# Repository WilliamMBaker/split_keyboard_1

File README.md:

# split_keyboard_1

Split keyboard project akin to [this](https://www.graz.io/articles/bayleaf-wireless-keyboard) one, and [this](https://github.com/merrittlj/aurora40) one.

## Requirements

- Split, preferably reversible PCBs or at least both sides be manufactured together and snapped/cut appart.
- Large battery, months long battery life.
- Wireless, bluetooth connection to target device.
- Plug and play, HID complient(?).
- Low profile, switches and keycaps.
- Ortholinear and no saggering.

## ErgoGen

[Link](https://ergogen.cache.works/).

## ZMK

[Link](https://zmk.dev/)

## Layout
[Link](https://www.keyboard-layout-editor.com/)

## Resources

- [Nice!Nano v2](https://mechboards.co.uk/products/nice-nano-v2)
- [Choc switches](https://typeractive.xyz/products/choc-switches)
- [Hot swap sockets](https://typeractive.xyz/products/hotswap-sockets?variant=45742200324327)
- [Switches](https://typeractive.xyz/products/mbk-keycaps)
- [Power switches](https://typeractive.xyz/products/power-switch)
- [Diods](https://typeractive.xyz/products/smd-diodes)

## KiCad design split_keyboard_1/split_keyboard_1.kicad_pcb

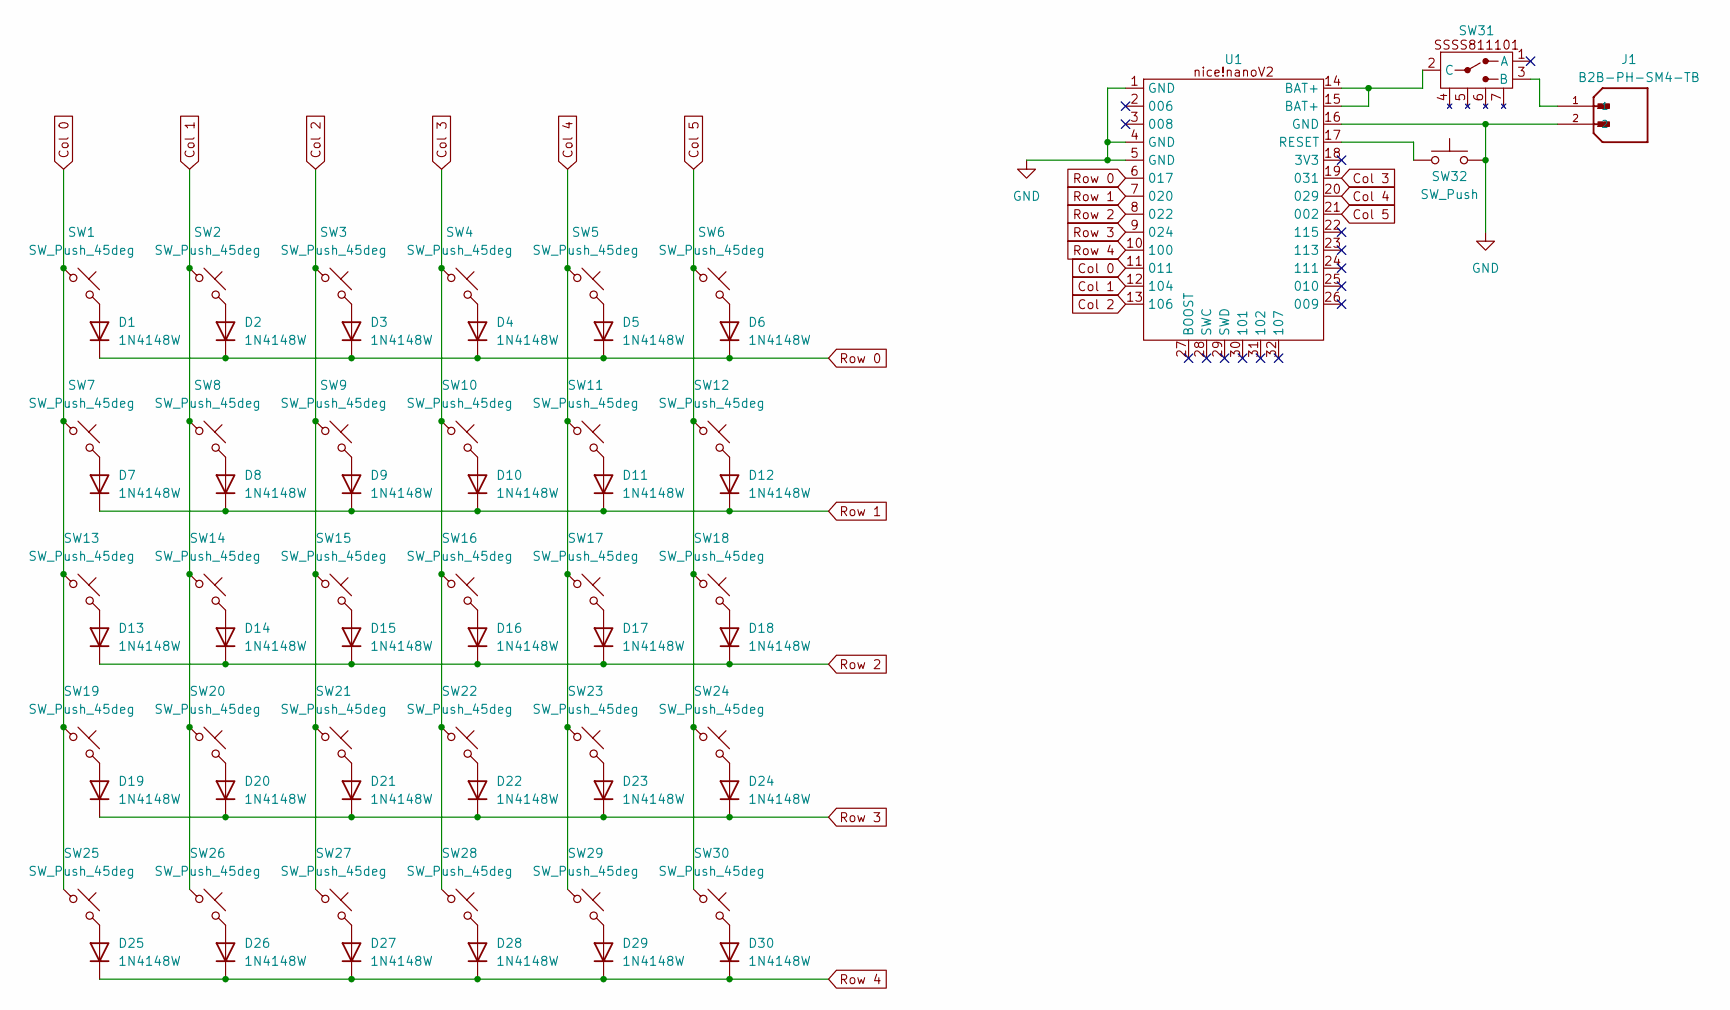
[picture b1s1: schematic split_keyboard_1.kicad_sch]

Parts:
D1, D2, D3, D4, D5, D6, D7, D8, D9, D10, D11, D12, D13, D14, D15, D16, D17, D18, D19, D20, D21, D22, D23, D24, D25, D26, D27, D28, D29, D30: 1N4148W; D_SOD-123
J1: B2B-PH-SM4-TB; JST_GH_SM02B-GHS-TB_1x02-1MP_P1.25mm_Horizontal; PARTREV N/A
SW1, SW2, SW3, SW4, SW5, SW6, SW7, SW8, SW9, SW10, SW11, SW12, SW13, SW14, SW15, SW16, SW17, SW18, SW19, SW20, SW21, SW22, SW23, SW24, SW25, SW26, SW27, SW28, SW29, SW30: SW_Push_45deg; SW_Hotswap_Kailh_Choc_V1_1.00u
SW31: SSSS811101_SW_SPDT
SW32: SW_Push; EVQPU_BTN
U1: nice!nanoV2

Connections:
Col 0: SW1.1, SW7.1, SW13.1, SW19.1, SW25.1, U1.11
Col 1: SW2.1, SW8.1, SW14.1, SW20.1, SW26.1, U1.12 (104)
Col 2: SW3.1, SW9.1, SW15.1, SW21.1, SW27.1, U1.13 (106)
Col 3: SW4.1, SW10.1, SW16.1, SW22.1, SW28.1, U1.19 (031)
Col 4: SW5.1, SW11.1, SW17.1, SW23.1, SW29.1, U1.20 (029)
Col 5: SW6.1, SW12.1, SW18.1, SW24.1, SW30.1, U1.21 (002)
GND: J1.2, SW32.2, U1.1 (GND), U1.4 (GND), U1.5 (GND), U1.16 (GND)
unnamed: D1.2 (A), SW1.2
unnamed: D2.2 (A), SW2.2
unnamed: D3.2 (A), SW3.2
unnamed: D4.2 (A), SW4.2
unnamed: D5.2 (A), SW5.2
unnamed: D6.2 (A), SW6.2
unnamed: D7.2 (A), SW7.2
unnamed: D8.2 (A), SW8.2
unnamed: D9.2 (A), SW9.2
unnamed: D10.2 (A), SW10.2
unnamed: D11.2 (A), SW11.2
unnamed: D12.2 (A), SW12.2
unnamed: D13.2 (A), SW13.2
unnamed: D14.2 (A), SW14.2
unnamed: D15.2 (A), SW15.2
unnamed: D16.2 (A), SW16.2
unnamed: D17.2 (A), SW17.2
unnamed: D18.2 (A), SW18.2
unnamed: D19.2 (A), SW19.2
unnamed: D20.2 (A), SW20.2
unnamed: D21.2 (A), SW21.2
unnamed: D22.2 (A), SW22.2
unnamed: D23.2 (A), SW23.2
unnamed: D24.2 (A), SW24.2
unnamed: D25.2 (A), SW25.2
unnamed: D26.2 (A), SW26.2
unnamed: D27.2 (A), SW27.2
unnamed: D28.2 (A), SW28.2
unnamed: D29.2 (A), SW29.2
unnamed: D30.2 (A), SW30.2
unnamed: J1.1, SW31.3 (B)
unnamed: SW31.2 (C), U1.14 (BAT+), U1.15 (BAT+)
unnamed: SW32.1, U1.17 (RESET)
Row 0: D1.1 (K), D2.1 (K), D3.1 (K), D4.1 (K), D5.1 (K), D6.1 (K), U1.6 (017)
Row 1: D7.1 (K), D8.1 (K), D9.1 (K), D10.1 (K), D11.1 (K), D12.1 (K), U1.7 (020)
Row 2: D13.1 (K), D14.1 (K), D15.1 (K), D16.1 (K), D17.1 (K), D18.1 (K), U1.8 (022)
Row 3: D19.1 (K), D20.1 (K), D21.1 (K), D22.1 (K), D23.1 (K), D24.1 (K), U1.9 (024)
Row 4: D25.1 (K), D26.1 (K), D27.1 (K), D28.1 (K), D29.1 (K), D30.1 (K), U1.10 (100)

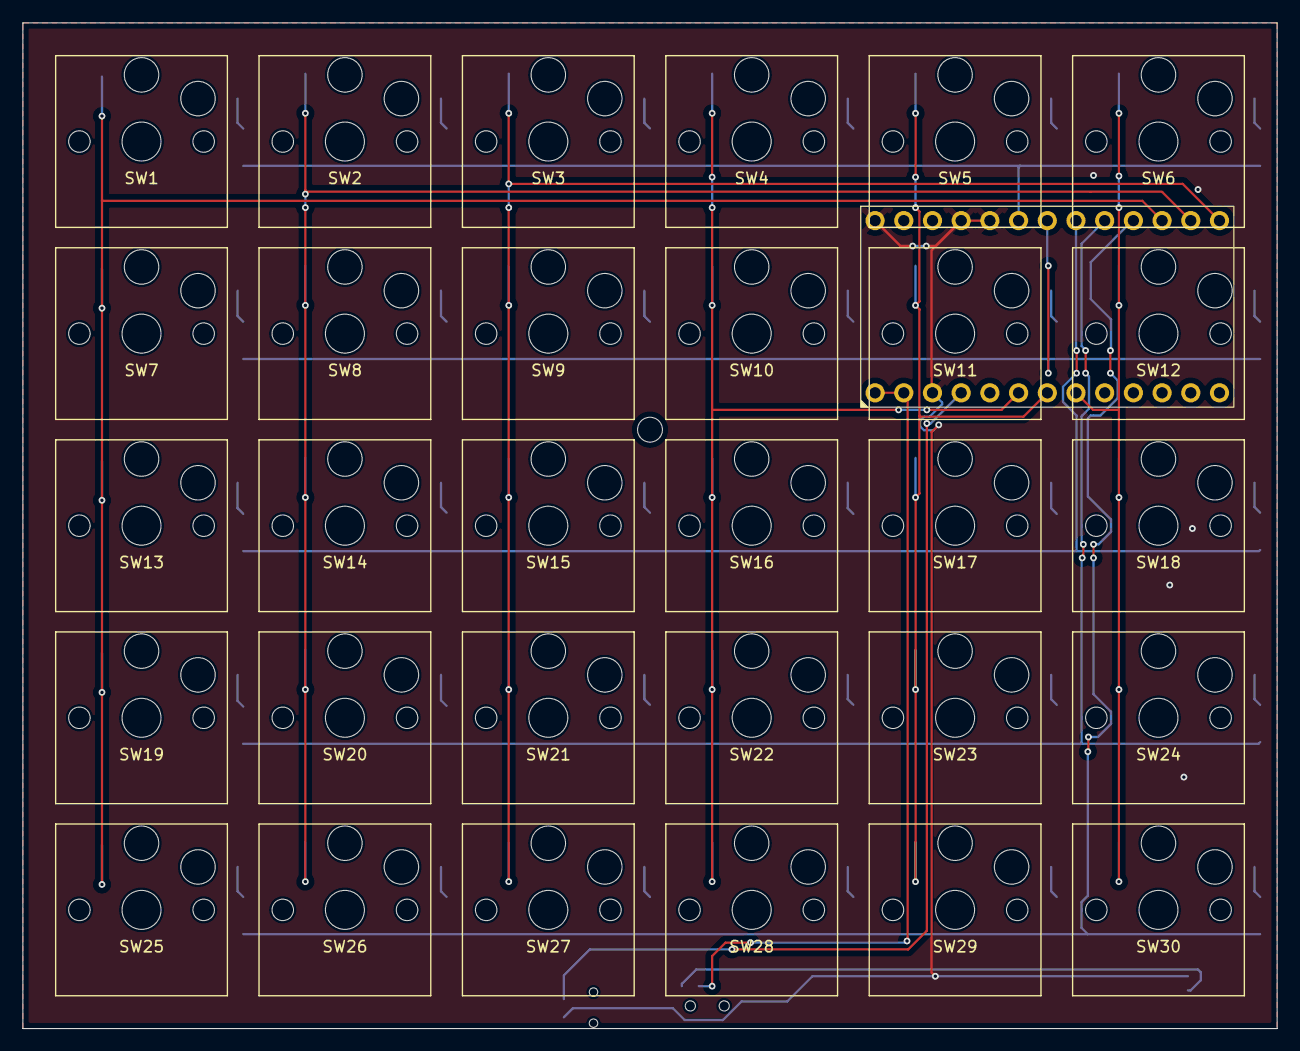
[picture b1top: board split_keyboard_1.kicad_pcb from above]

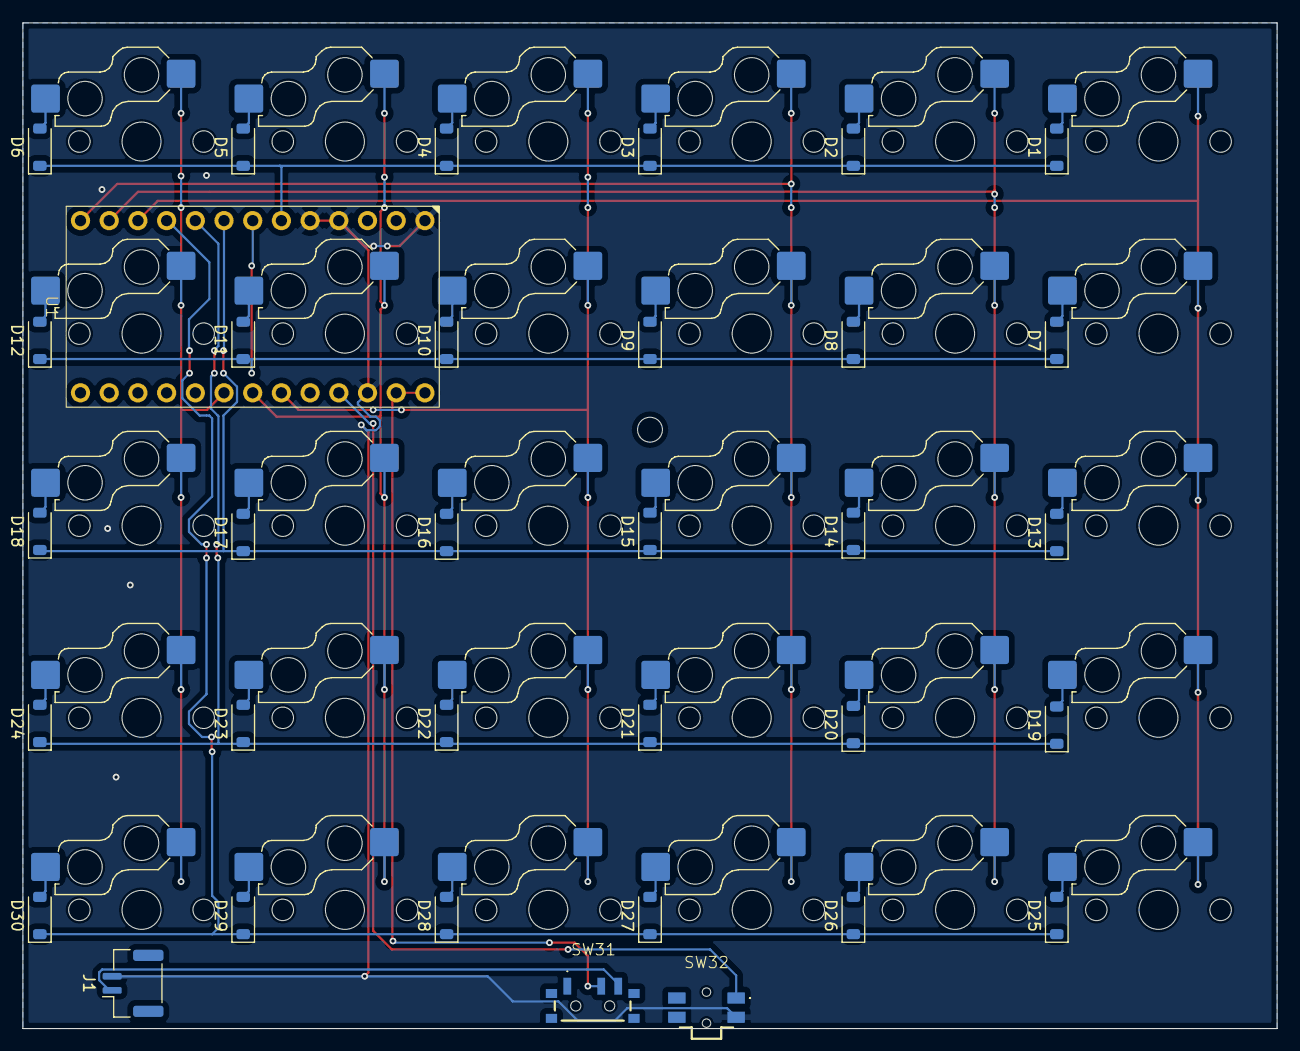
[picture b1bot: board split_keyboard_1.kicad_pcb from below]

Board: 2 copper layers, 111.0 x 89.0 mm, 64 parts (34 on the bottom side), 45 nets.

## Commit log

2025-09-03 Create nice!nanoV2 schematic and start on footprint
2025-09-04 Add switches, fill out nice!nanoV2 symbol
2025-09-05 on/off switch symbol and start on footprint
2025-09-06 Add reset and power switch
2025-09-06 Add centre screw hole
2025-09-07 Add 3D models to power and reset switches
2025-09-07 move switches to edge
2025-09-07 add ground plane
2025-09-16 Add 3d models
